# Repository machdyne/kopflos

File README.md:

# Kopflos Computer

Kopflos is a headless FPGA computer designed by Lone Dynamics Corporation.

This repo contains schematics, PCB layouts, pinouts, a 3D-printable case, example gateware and documentation.

Find more information on the [Kopflos product page](https://machdyne.com/product/kopflos-computer/).

## Programming Kopflos

Kopflos has a JTAG interface and ships with a [DFU bootloader](https://github.com/machdyne/tinydfu-bootloader) that allows the included flash [MMOD](https://machdyne.com/product/mmod) to be programmed over the USB-C port.

### DFU

The DFU bootloader is available for 5 seconds after power-on, issuing a DFU command during this period will stop the boot process until the DFU device is detached. If no command is received the boot process will continue and the user gateware will be loaded.

Install [dfu-util](http://dfu-util.sourceforge.net) (Debian/Ubuntu):

```
$ sudo apt install dfu-util
```

Update the user gateware on the flash MMOD:

```
$ sudo dfu-util -a 0 -D image.bit
```

Detach the DFU device and continue the boot process:

```
$ sudo dfu-util -a 0 -e
```

It is possible to update the bootloader itself using DFU but you shouldn't attempt this unless you have a JTAG programmer (or another method to program the MMOD) available, in case you need to restore the bootloader.

### JTAG

These examples assume you're using a "USB Blaster" JTAG cable, see the header pinout below. You will need to have [openFPGALoader](https://github.com/trabucayre/openFPGALoader) installed.

Program the configuration SRAM:

```
openFPGALoader -c usb-blaster image.bit
```

Program the flash MMOD:

```
openFPGALoader -f -c usb-blaster images/bootloader/tinydfu_kopflos.bit
```

## Blinky 

Building the blinky example requires [Yosys](https://github.com/YosysHQ/yosys), [nextpnr-ecp5](https://github.com/YosysHQ/nextpnr) and [Project Trellis](https://github.com/YosysHQ/prjtrellis).

Assuming they are installed, you can simply type `make` to build the gateware, which will be written to output/blinky.bin. You can then use [openFPGALoader](https://github.com/trabucayre/openFPGALoader) or dfu-util to write the gateware to the device.

## Linux

See the [Kakao Linux](https://github.com/machdyne/kakao) repo for detailed installation instructions.

## JTAG Header

The 3.3V JTAG header can be used to program the FPGA SRAM as well as the MMOD flash memory.

```
2 4 6
1 3 5
```

| Pin | Signal |
| --- | ------ |
| 1 | TCK |
| 2 | TDI |
| 3 | TDO |
| 4 | TMS |
| 5 | 3V3 (out) |
| 6 | GND |

## Board Revisions

| Revision | Notes |
| -------- | ----- |
| V0 | Initial version |

## License

The contents of this repo are released under the [Lone Dynamics Open License](LICENSE.md) with the following exceptions:

- The KiCad design files contain parts of the [kicad-pmod](https://github.com/mithro/kicad-pmod) library which is released under the [Apache License, Version 2.0](https://www.apache.org/licenses/LICENSE-2.0.html).

- The KiCad design files may contain symbols and footprints released under other licenses; please contact us if we've failed to give proper attribution.

Note: You can use these designs for commercial purposes but we ask that instead of producing exact clones, that you either replace our trademarks and logos with your own or add your own next to ours.

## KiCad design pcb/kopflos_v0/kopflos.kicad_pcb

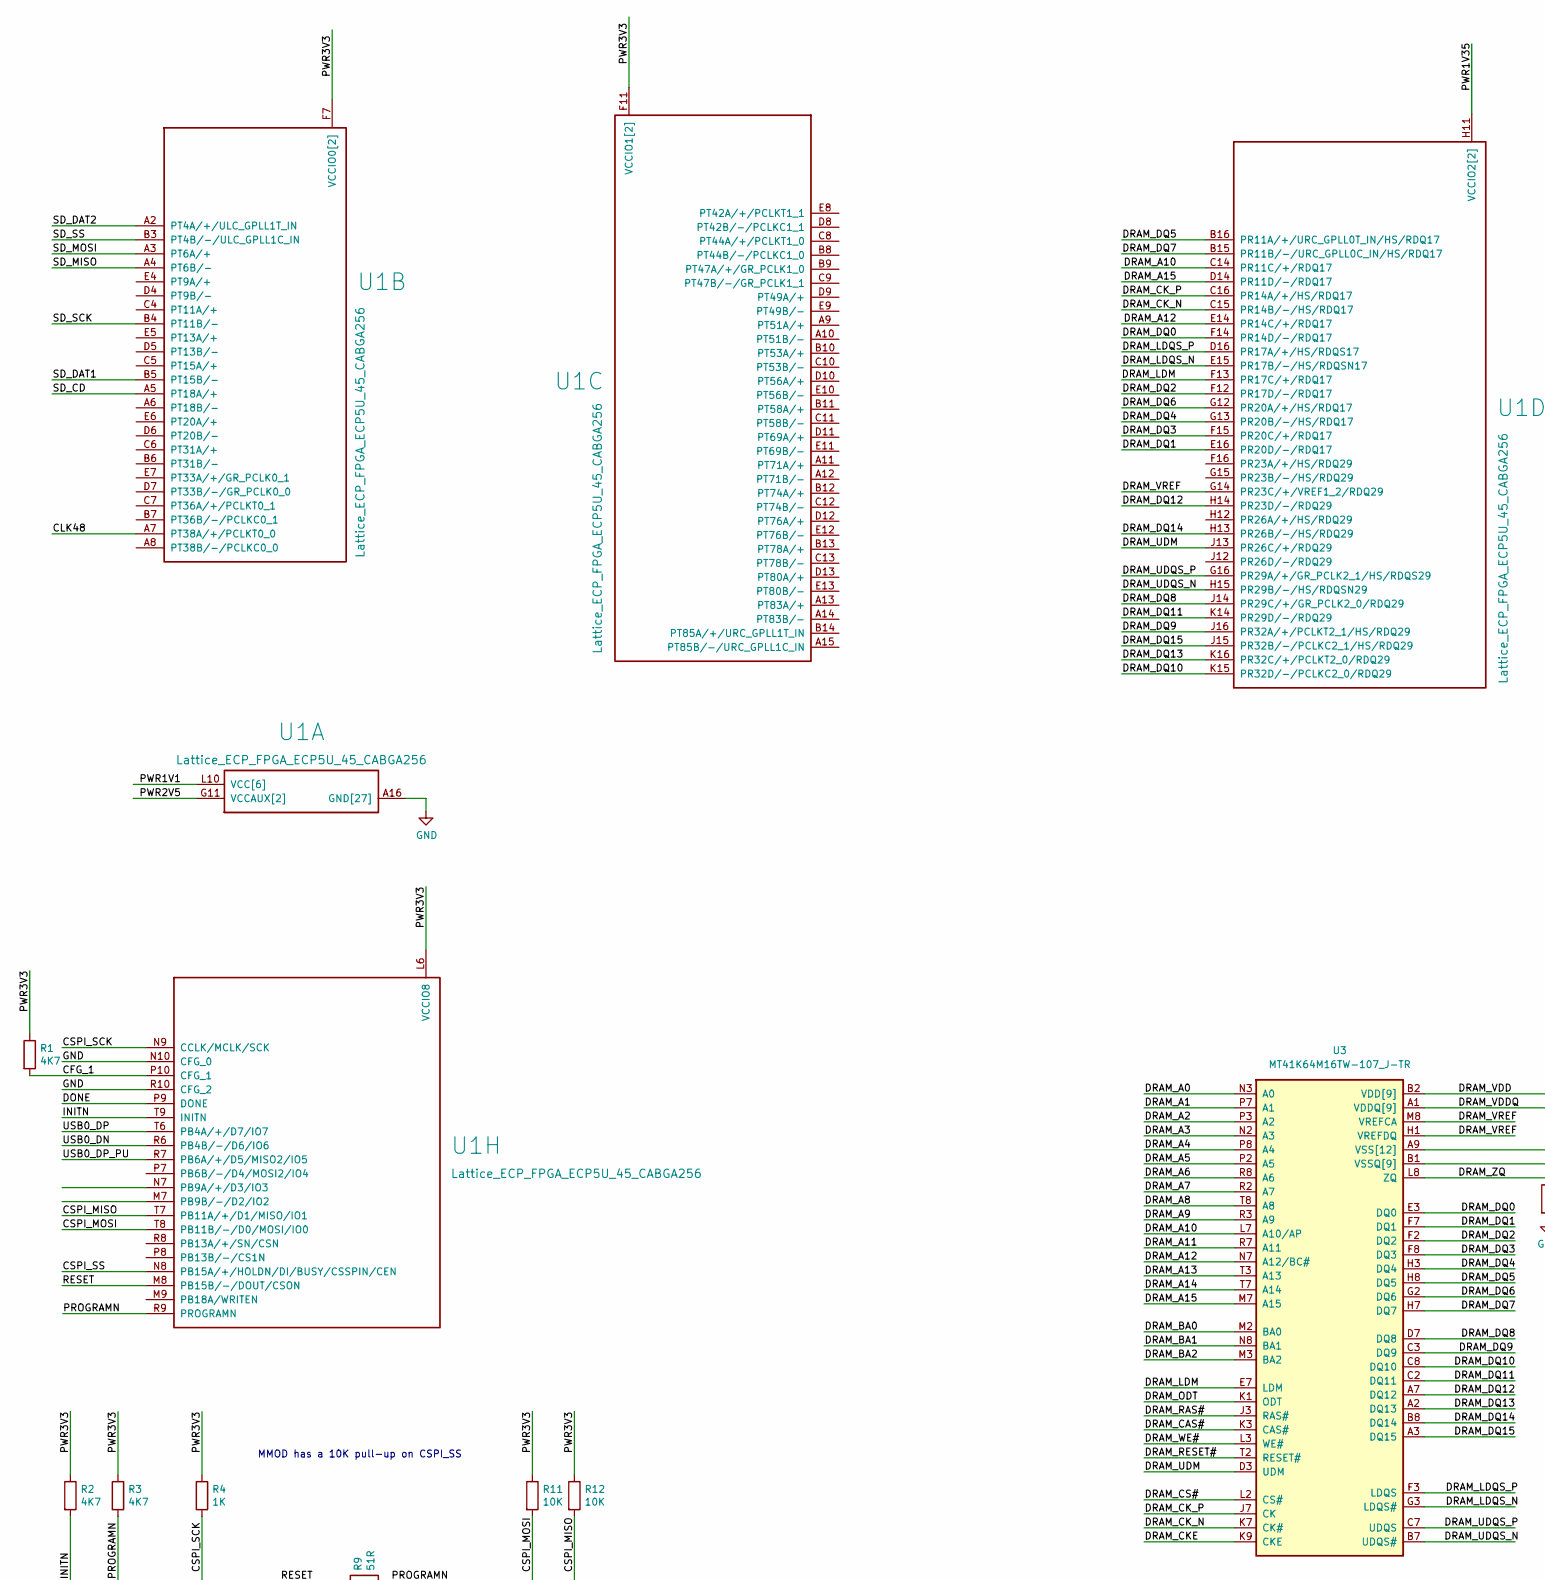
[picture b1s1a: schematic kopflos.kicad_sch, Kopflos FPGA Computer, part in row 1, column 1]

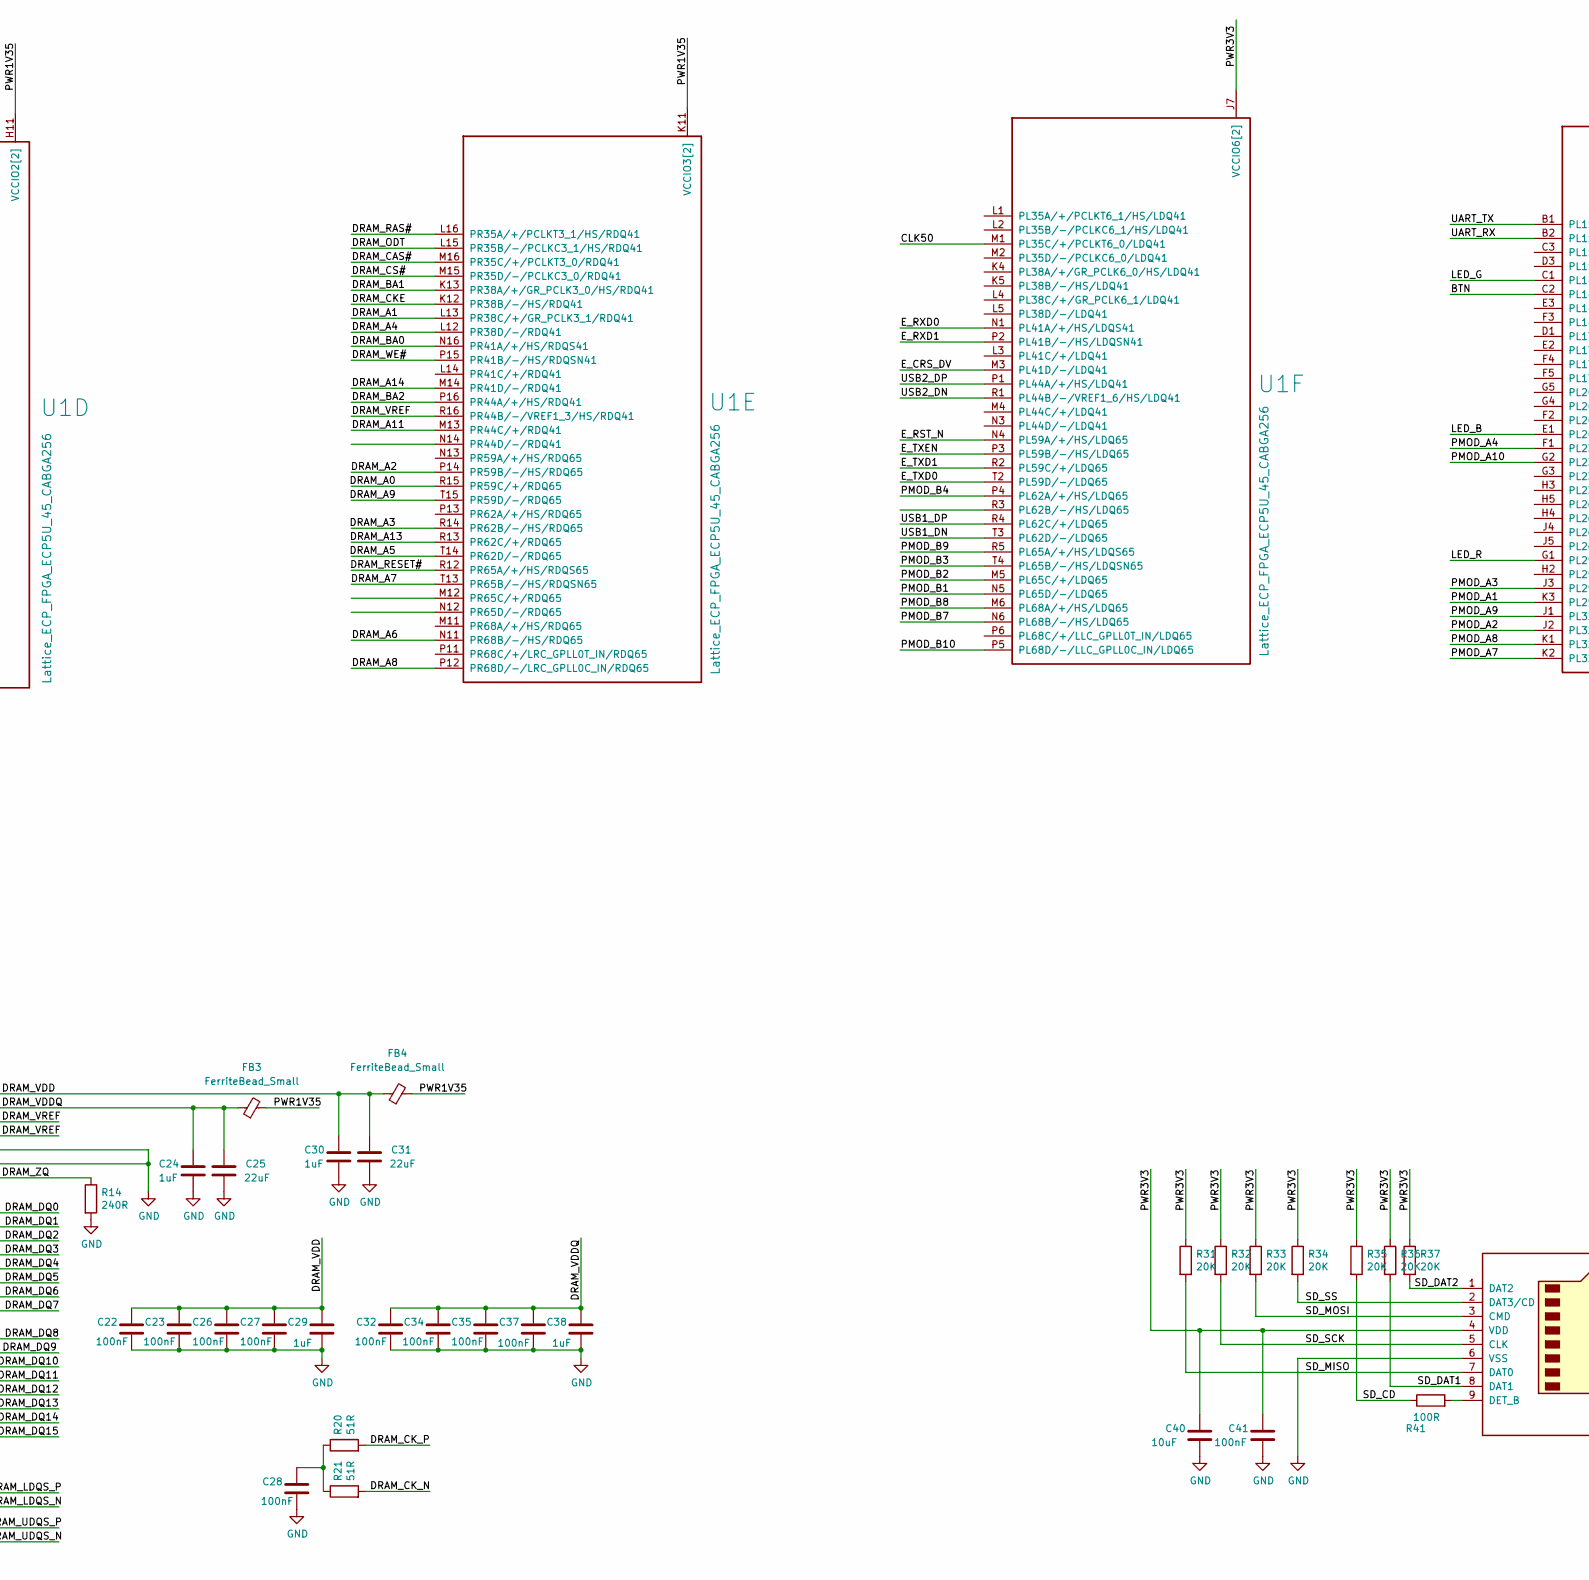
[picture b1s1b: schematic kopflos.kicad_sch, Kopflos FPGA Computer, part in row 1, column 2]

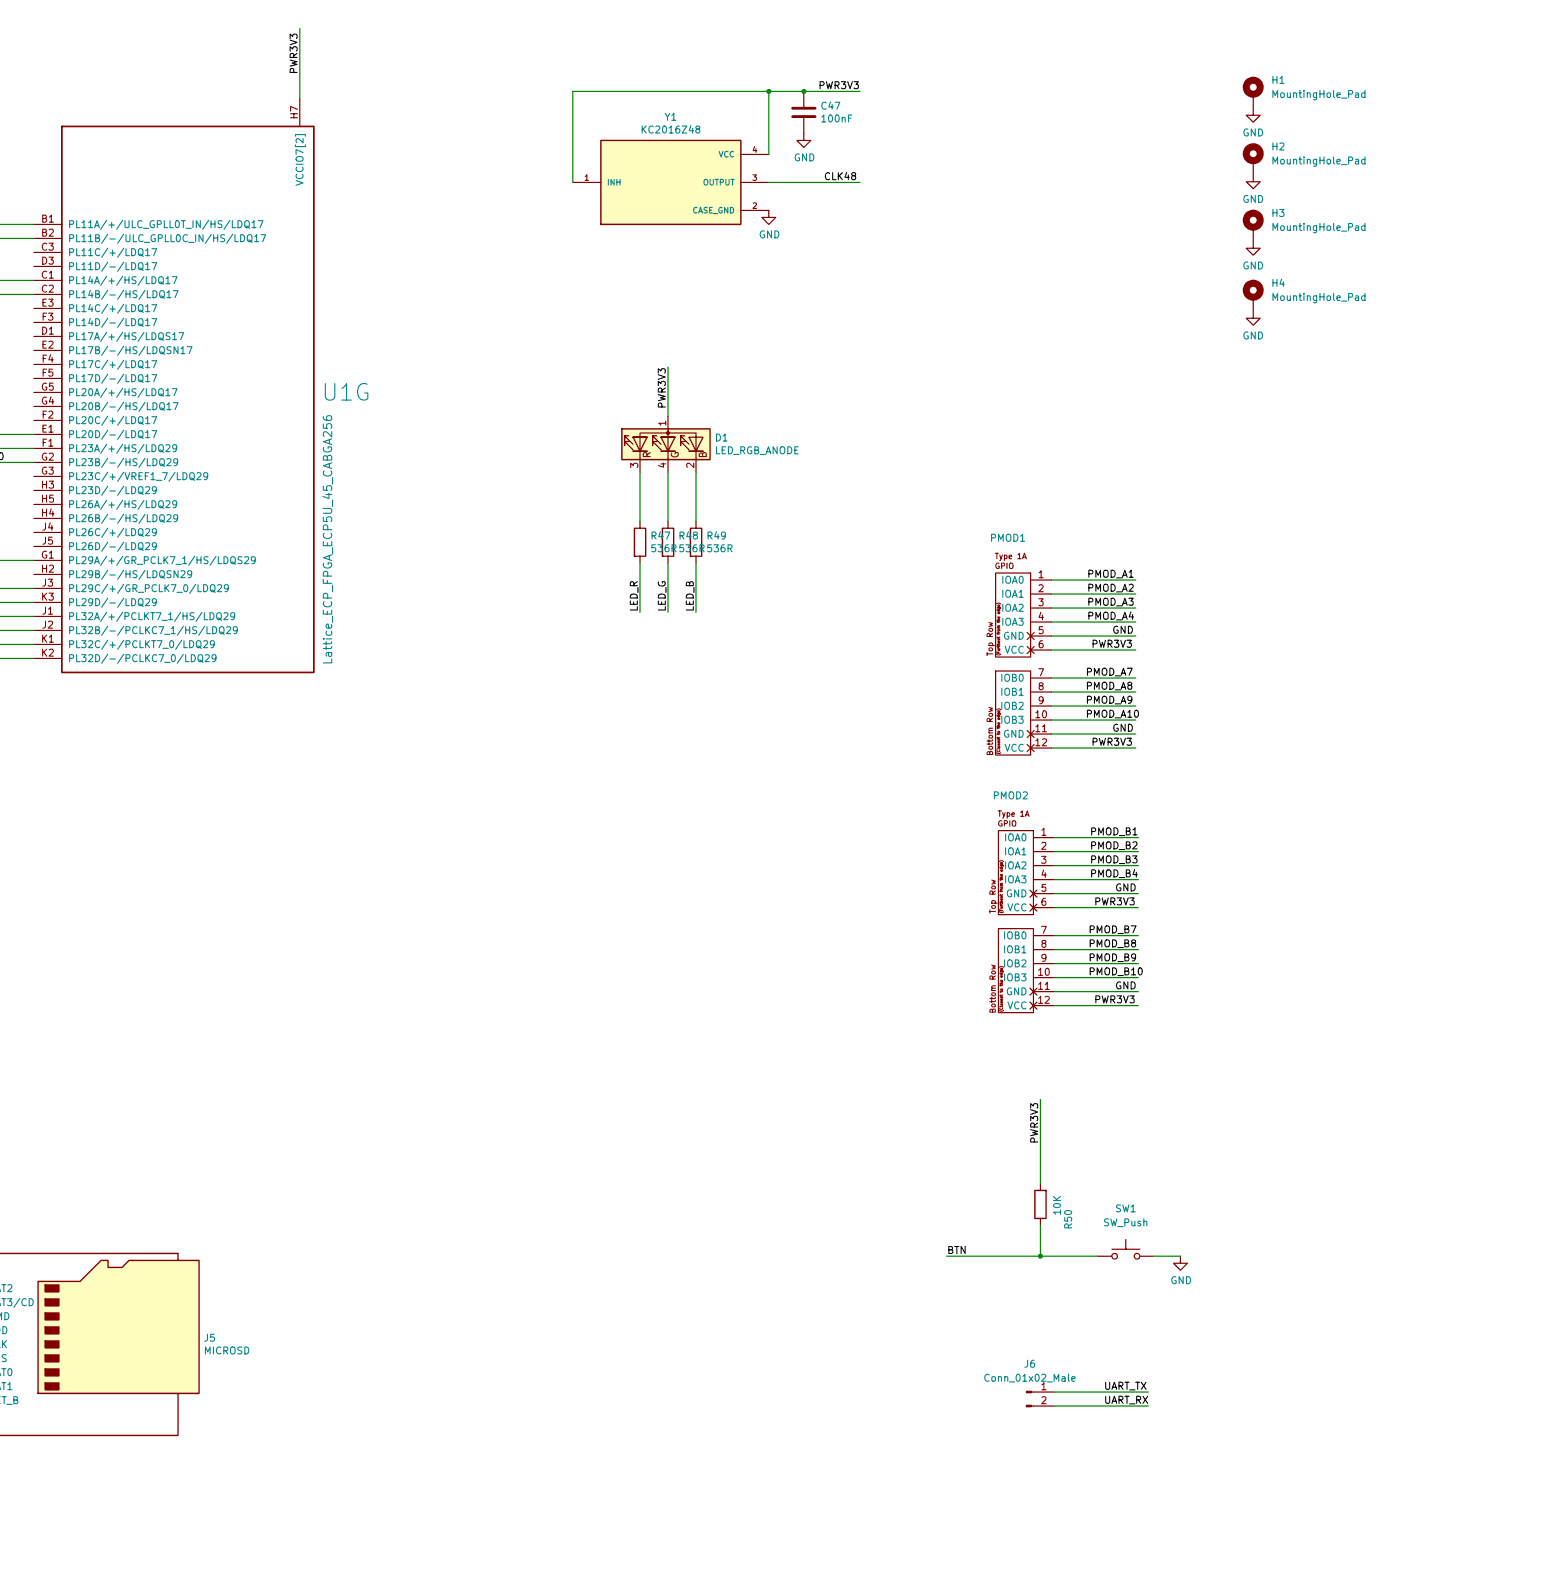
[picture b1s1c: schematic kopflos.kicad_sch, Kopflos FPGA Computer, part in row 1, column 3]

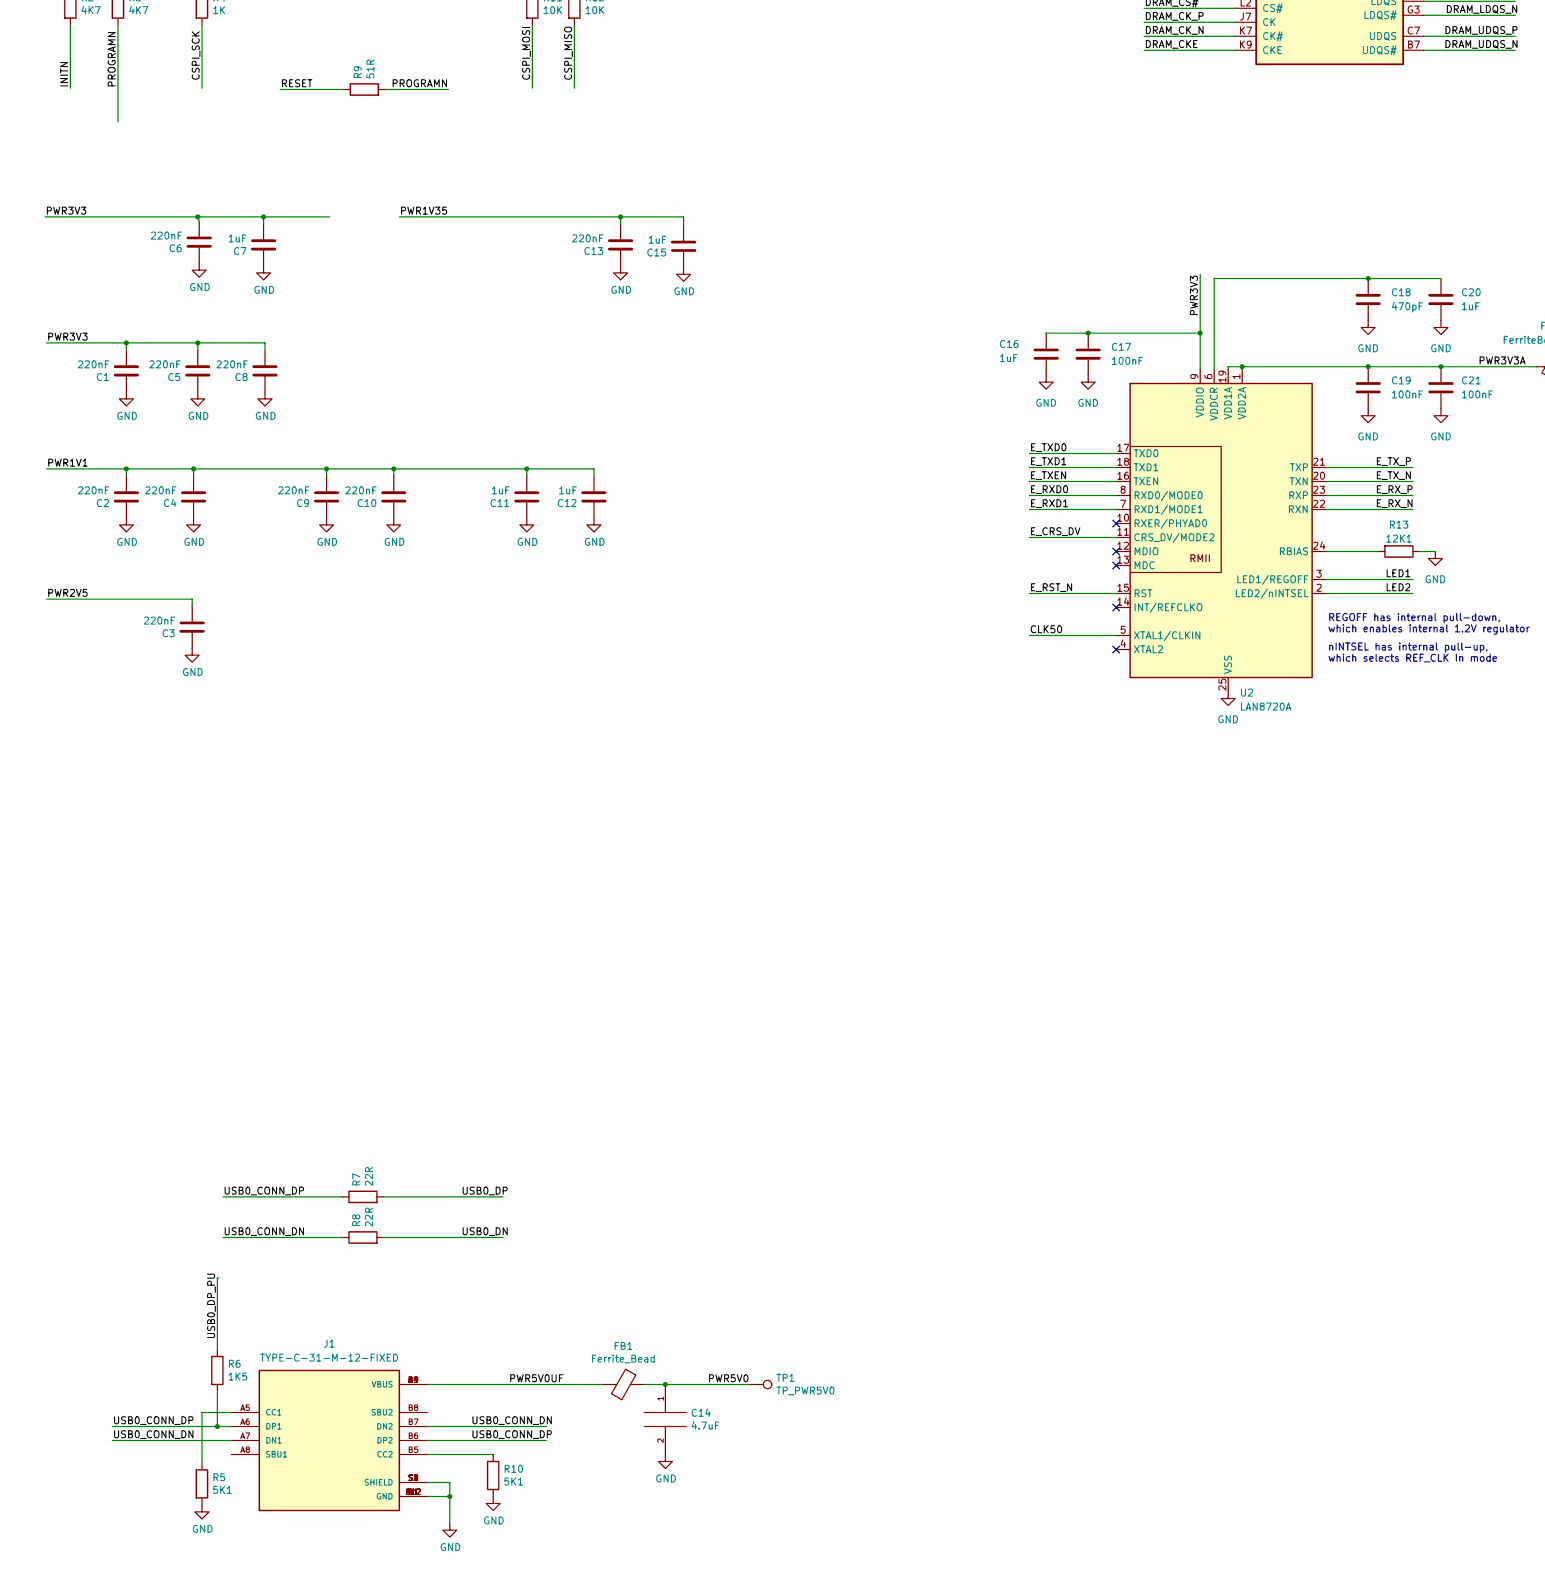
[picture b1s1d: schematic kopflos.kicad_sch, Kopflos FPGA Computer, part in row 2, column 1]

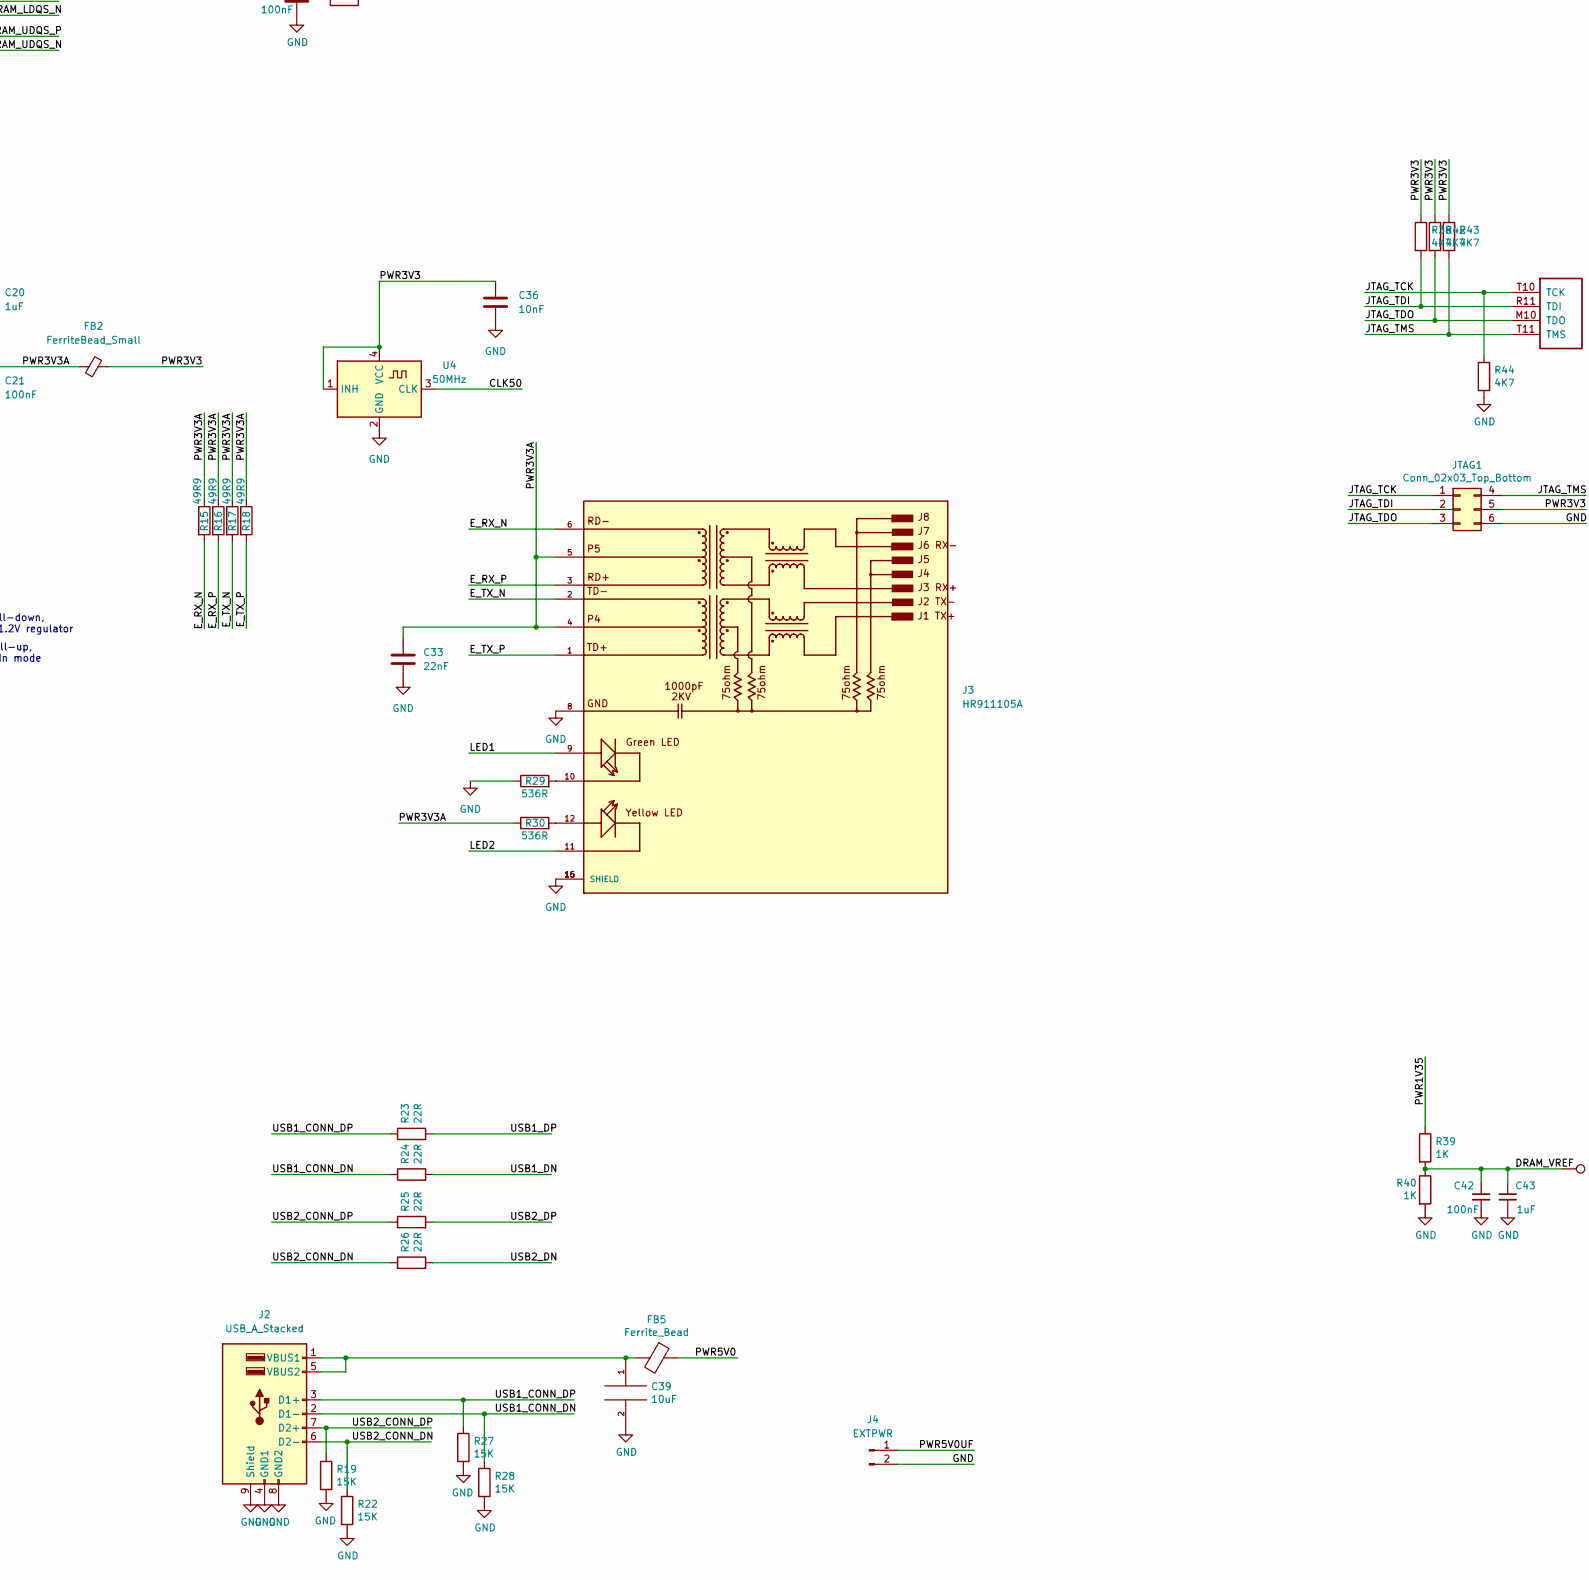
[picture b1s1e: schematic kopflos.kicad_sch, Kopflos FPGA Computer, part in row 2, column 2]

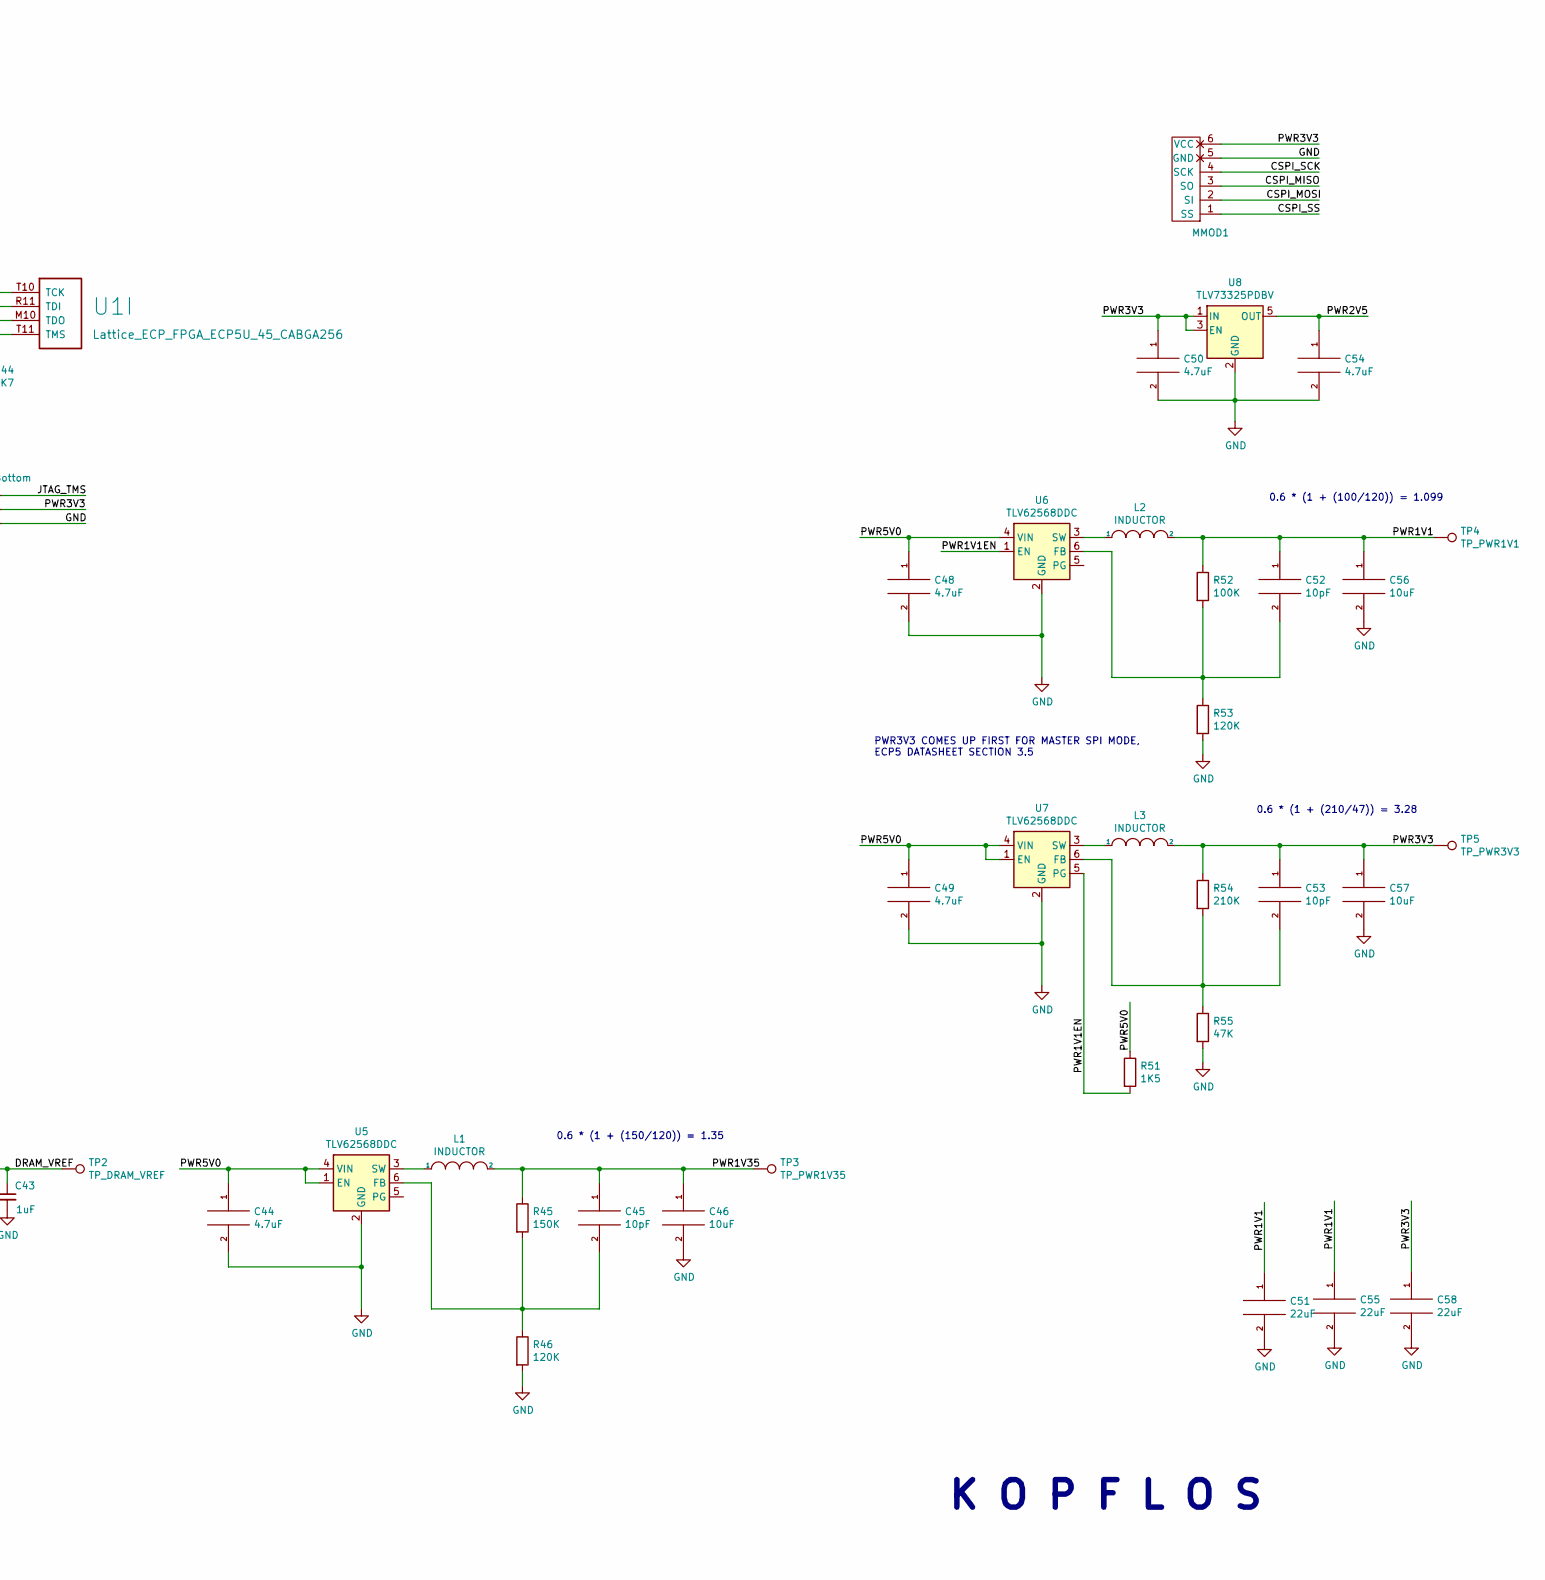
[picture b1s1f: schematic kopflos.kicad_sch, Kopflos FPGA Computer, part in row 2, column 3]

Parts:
C1, C2, C3, C4, C5, C6, C8, C9, C10, C13: 220nF; C_0603_1608Metric
C7, C11, C12, C15, C20, C43: 1uF; C_0603_1608Metric
C14, C44, C48, C49, C50, C54: 4.7uF; C_0603_1608Metric
C16, C24, C29, C30, C38: 1uF; C_0402_1005Metric
C17, C22, C23, C26, C27, C32, C34, C35, C37: 100nF; C_0402_1005Metric
C18: 470pF; C_0603_1608Metric
C19, C21, C42, C47: 100nF; C_0603_1608Metric
C25, C31: 22uF; R_0603_1608Metric
C28, C41: 100nF; R_0603_1608Metric
C33: 22nF; C_0603_1608Metric
C36: 10nF; C_0603_1608Metric
C39, C46, C56, C57: 10uF; C_0603_1608Metric
C40: 10uF; R_0603_1608Metric
C45, C52, C53: 10pF; C_0603_1608Metric
C51, C55, C58: 22uF; C_0603_1608Metric
D1: LED_RGB_ANODE; LED_RGB_0606_CHANZON
FB1, FB5: Ferrite_Bead; R_0603_1608Metric
FB2, FB3, FB4: FerriteBead_Small; R_0603_1608Metric
H1, H2, H3, H4: MountingHole_Pad; MountingHole_3.2mm_M3_Pad
J1: TYPE-C-31-M-12-FIXED; USB_C_Receptacle_HRO_TYPE-C-31-M-12-BIG-PADS; PARTREV A
J2: USB_A_Stacked; USB_A_Wuerth_61400826021_Horizontal_Stacked
J3: HR911105A; HANRUN_HR911105A; PARTREV A
J4: EXTPWR; PinHeader_1x02_P2.54mm_Vertical
J5: MICROSD; SDCARD
J6: Conn_01x02_Male; PinHeader_1x02_P2.54mm_Vertical
JTAG1: Conn_02x03_Top_Bottom; PinHeader_2x03_P2.54mm_Vertical
L1, L2, L3: INDUCTOR; L_0805_2012Metric
MMOD1: PMOD-Device-x1-Type-2-SPI; MMOD_Host_Socket
PMOD1, PMOD2: PMOD-Device-x2-Type-1A-GPIO; PMOD_2x06_HOST
R1, R2, R3, R38, R42, R43, R44: 4K7; R_0603_1608Metric
R4, R39, R40: 1K; R_0603_1608Metric
R5, R10: 5K1; R_0603_1608Metric
R6: 1K5; R_0402_1005Metric
R7, R8, R23, R24, R25, R26: 22R; R_0603_1608Metric
R9, R20, R21: 51R; R_0603_1608Metric
R11, R12, R50: 10K; R_0603_1608Metric
R13: 12K1; R_0603_1608Metric
R14: 240R; R_0603_1608Metric
R15, R16, R17, R18: 49R9; R_0603_1608Metric
R19, R22, R27, R28: 15K; R_0402_1005Metric
R29, R30, R47, R48, R49: 536R; R_0603_1608Metric
R31, R32, R33, R34, R35, R36, R37: 20K; R_0603_1608Metric
R41: 100R; R_0603_1608Metric
R45: 150K; R_0603_1608Metric
R46, R53: 120K; R_0603_1608Metric
R51: 1K5; R_0603_1608Metric
R52: 100K; R_0603_1608Metric
R54: 210K; R_0603_1608Metric
R55: 47K; R_0603_1608Metric
SW1: SW_Push; Button_2P_3x4mm
TP1: TP_PWR5V0; TestPoint_THTPad_D1.0mm_Drill0.5mm
TP2: TP_DRAM_VREF; TestPoint_THTPad_D1.0mm_Drill0.5mm
TP3: TP_PWR1V35; TestPoint_THTPad_D1.0mm_Drill0.5mm
TP4: TP_PWR1V1; TestPoint_THTPad_D1.0mm_Drill0.5mm
TP5: TP_PWR3V3; TestPoint_THTPad_D1.0mm_Drill0.5mm
U1: Lattice_ECP_FPGA_ECP5U_45_CABGA256; BGA-256_14.0x14.0mm_Layout16x16_P0.8mm_Ball0.45mm_Pad0.32mm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
U2: LAN8720A; QFN-24-1EP_4x4mm_P0.5mm_EP2.6x2.6mm
U3: MT41K64M16TW-107_J-TR; BGA-96_9.0x13.0mm_Layout2x3x16_P0.8mm
U4: 50MHz; Oscillator_SMD_Kyocera_KC2520Z-4Pin_2.5x2.0mm
U5, U6, U7: TLV62568DDC; SOT-23-6
U8: TLV73325PDBV; SOT-23-5
Y1: KC2016Z48; OSC_KC2016Z13.5600C1KX00; PARTREV November 2020

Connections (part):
/BTN: R50.1, SW1.1, U1.C2 (PL14B/-/HS/LDQ17)
/CFG_1: R1.2, U1.P10 (CFG_1)
/CLK48: U1.A7 (PT38A/+/PCLKT0_0), Y1.3 (OUTPUT)
/CLK50: U1.M1 (PL35C/+/PCLKT6_0/LDQ41), U2.5 (XTAL1/CLKIN), U4.3 (CLK)
/CSPI_MISO: MMOD1.3 (SO), R12.2, U1.T7 (PB11A/+/D1/MISO/IO1)
/CSPI_MOSI: MMOD1.2 (SI), R11.2, U1.T8 (PB11B/-/D0/MOSI/IO0)
/CSPI_SCK: MMOD1.4 (SCK), R4.2, U1.N9 (CCLK/MCLK/SCK)
/CSPI_SS: MMOD1.1 (SS), U1.N8 (PB15A/+/HOLDN/DI/BUSY/CSSPIN/CEN)
/DONE: U1.P9 (DONE)
/DRAM_A0: U1.R15 (PR59C/+/RDQ65), U3.N3 (A0)
/DRAM_A1: U1.L13 (PR38C/+/GR_PCLK3_1/RDQ41), U3.P7 (A1)
/DRAM_A2: U1.P14 (PR59B/-/HS/RDQ65), U3.P3 (A2)
/DRAM_A3: U1.R14 (PR62B/-/HS/RDQ65), U3.N2 (A3)
/DRAM_A4: U1.L12 (PR38D/-/RDQ41), U3.P8 (A4)
/DRAM_A5: U1.T14 (PR62D/-/RDQ65), U3.P2 (A5)
/DRAM_A6: U1.N11 (PR68B/-/HS/RDQ65), U3.R8 (A6)
/DRAM_A7: U1.T13 (PR65B/-/HS/RDQSN65), U3.R2 (A7)
/DRAM_A8: U1.P12 (PR68D/-/LRC_GPLL0C_IN/RDQ65), U3.T8 (A8)
/DRAM_A9: U1.T15 (PR59D/-/RDQ65), U3.R3 (A9)
/DRAM_A10: U1.C14 (PR11C/+/RDQ17), U3.L7 (A10/AP)
/DRAM_A11: U1.M13 (PR44C/+/RDQ41), U3.R7 (A11)
/DRAM_A12: U1.E14 (PR14C/+/RDQ17), U3.N7 (A12/BC#)
/DRAM_A13: U1.R13 (PR62C/+/RDQ65), U3.T3 (A13)
/DRAM_A14: U1.M14 (PR41D/-/RDQ41), U3.T7 (A14)
/DRAM_A15: U1.D14 (PR11D/-/RDQ17), U3.M7 (A15)
/DRAM_BA0: U1.N16 (PR41A/+/HS/RDQS41), U3.M2 (BA0)
/DRAM_BA1: U1.K13 (PR38A/+/GR_PCLK3_0/HS/RDQ41), U3.N8 (BA1)
/DRAM_BA2: U1.P16 (PR44A/+/HS/RDQ41), U3.M3 (BA2)
/DRAM_CAS#: U1.M16 (PR35C/+/PCLKT3_0/RDQ41), U3.K3 (CAS#)
/DRAM_CKE: U1.K12 (PR38B/-/HS/RDQ41), U3.K9 (CKE)
/DRAM_CK_N: R21.2, U1.C15 (PR14B/-/HS/RDQ17), U3.K7 (CK#)
/DRAM_CK_P: R20.2, U1.C16 (PR14A/+/HS/RDQ17), U3.J7 (CK)
/DRAM_CS#: U1.M15 (PR35D/-/PCLKC3_0/RDQ41), U3.L2 (CS#)
/DRAM_DQ0: U1.F14 (PR14D/-/RDQ17), U3.E3 (DQ0)
/DRAM_DQ1: U1.E16 (PR20D/-/RDQ17), U3.F7 (DQ1)
/DRAM_DQ2: U1.F12 (PR17D/-/RDQ17), U3.F2 (DQ2)
/DRAM_DQ3: U1.F15 (PR20C/+/RDQ17), U3.F8 (DQ3)
/DRAM_DQ4: U1.G13 (PR20B/-/HS/RDQ17), U3.H3 (DQ4)
/DRAM_DQ5: U1.B16 (PR11A/+/URC_GPLL0T_IN/HS/RDQ17), U3.H8 (DQ5)
/DRAM_DQ6: U1.G12 (PR20A/+/HS/RDQ17), U3.G2 (DQ6)
/DRAM_DQ7: U1.B15 (PR11B/-/URC_GPLL0C_IN/HS/RDQ17), U3.H7 (DQ7)
/DRAM_DQ8: U1.J14 (PR29C/+/GR_PCLK2_0/RDQ29), U3.D7 (DQ8)
/DRAM_DQ9: U1.J16 (PR32A/+/PCLKT2_1/HS/RDQ29), U3.C3 (DQ9)
/DRAM_DQ10: U1.K15 (PR32D/-/PCLKC2_0/RDQ29), U3.C8 (DQ10)
/DRAM_DQ11: U1.K14 (PR29D/-/RDQ29), U3.C2 (DQ11)
/DRAM_DQ12: U1.H14 (PR23D/-/RDQ29), U3.A7 (DQ12)
/DRAM_DQ13: U1.K16 (PR32C/+/PCLKT2_0/RDQ29), U3.A2 (DQ13)
/DRAM_DQ14: U1.H13 (PR26B/-/HS/RDQ29), U3.B8 (DQ14)
/DRAM_DQ15: U1.J15 (PR32B/-/PCLKC2_1/HS/RDQ29), U3.A3 (DQ15)
/DRAM_LDM: U1.F13 (PR17C/+/RDQ17), U3.E7 (LDM)
/DRAM_LDQS_N: U1.E15 (PR17B/-/HS/RDQSN17), U3.G3 (LDQS#)
/DRAM_LDQS_P: U1.D16 (PR17A/+/HS/RDQS17), U3.F3 (LDQS)
/DRAM_ODT: U1.L15 (PR35B/-/PCLKC3_1/HS/RDQ41), U3.K1 (ODT)
/DRAM_RAS#: U1.L16 (PR35A/+/PCLKT3_1/HS/RDQ41), U3.J3 (RAS#)
/DRAM_RESET#: U1.R12 (PR65A/+/HS/RDQS65), U3.T2 (RESET#)
/DRAM_UDM: U1.J13 (PR26C/+/RDQ29), U3.D3 (UDM)
/DRAM_UDQS_N: U1.H15 (PR29B/-/HS/RDQSN29), U3.B7 (UDQS#)
/DRAM_UDQS_P: U1.G16 (PR29A/+/GR_PCLK2_1/HS/RDQS29), U3.C7 (UDQS)
/DRAM_VDD: C22.1, C23.1, C26.1, C27.1, C29.1, C30.1, C31.1, FB4.1, U3.B2 (VDD[9]), U3.D9 (VDD), U3.G7 (VDD), U3.K2 (VDD), U3.K8 (VDD), U3.N1 (VDD), U3.N9 (VDD), U3.R1 (VDD), U3.R9 (VDD)
/DRAM_VDDQ: C24.1, C25.1, C32.1, C34.1, C35.1, C37.1, C38.1, FB3.1, U3.A1 (VDDQ[9]), U3.A8 (VDDQ), U3.C1 (VDDQ), U3.C9 (VDDQ), U3.D2 (VDDQ), U3.E9 (VDDQ), U3.F1 (VDDQ), U3.H2 (VDDQ), U3.H9 (VDDQ)
/DRAM_VREF: C42.1, C43.1, R39.2, R40.1, TP2.1, U1.G14 (PR23C/+/VREF1_2/RDQ29), U1.R16 (PR44B/-/VREF1_3/HS/RDQ41), U3.H1 (VREFDQ), U3.M8 (VREFCA)
/DRAM_WE#: U1.P15 (PR41B/-/HS/RDQSN41), U3.L3 (WE#)
/DRAM_ZQ: R14.1, U3.L8 (ZQ)
/E_CRS_DV: U1.M3 (PL41D/-/LDQ41), U2.11 (CRS_DV/MODE2)
/E_RST_N: U1.N4 (PL59A/+/HS/LDQ65), U2.15 (RST)
/E_RXD0: U1.N1 (PL41A/+/HS/LDQS41), U2.8 (RXD0/MODE0)
/E_RXD1: U1.P2 (PL41B/-/HS/LDQSN41), U2.7 (RXD1/MODE1)
/E_RX_N: J3.6, R15.2, U2.22 (RXN)
/E_RX_P: J3.3, R16.2, U2.23 (RXP)
/E_TXD0: U1.T2 (PL59D/-/LDQ65), U2.17 (TXD0)
/E_TXD1: U1.R2 (PL59C/+/LDQ65), U2.18 (TXD1)
/E_TXEN: U1.P3 (PL59B/-/HS/LDQ65), U2.16 (TXEN)
/E_TX_N: J3.2, R17.2, U2.20 (TXN)
/E_TX_P: J3.1, R18.2, U2.21 (TXP)
/INITN: R2.2, U1.T9 (INITN)
/JTAG_TCK: JTAG1.1, R44.1, U1.T10 (TCK)
/JTAG_TDI: JTAG1.2, R38.2, U1.R11 (TDI)
/JTAG_TDO: JTAG1.3, R42.2, U1.M10 (TDO)
/JTAG_TMS: JTAG1.4, R43.2, U1.T11 (TMS)
/LED1: J3.9, U2.3 (LED1/REGOFF)
/LED2: J3.11, U2.2 (LED2/nINTSEL)
/LED_B: R49.2, U1.E1 (PL20D/-/LDQ17)
/LED_G: R48.2, U1.C1 (PL14A/+/HS/LDQ17)
/LED_R: R47.2, U1.G1 (PL29A/+/GR_PCLK7_1/HS/LDQS29)
/PMOD_A1: PMOD1.1 (IOA0), U1.K3 (PL29D/-/LDQ29)
/PMOD_A2: PMOD1.2 (IOA1), U1.J2 (PL32B/-/PCLKC7_1/HS/LDQ29)
/PMOD_A3: PMOD1.3 (IOA2), U1.J3 (PL29C/+/GR_PCLK7_0/LDQ29)
/PMOD_A4: PMOD1.4 (IOA3), U1.F1 (PL23A/+/HS/LDQ29)
/PMOD_A7: PMOD1.7 (IOB0), U1.K2 (PL32D/-/PCLKC7_0/LDQ29)
/PMOD_A8: PMOD1.8 (IOB1), U1.K1 (PL32C/+/PCLKT7_0/LDQ29)
/PMOD_A9: PMOD1.9 (IOB2), U1.J1 (PL32A/+/PCLKT7_1/HS/LDQ29)
/PMOD_A10: PMOD1.10 (IOB3), U1.G2 (PL23B/-/HS/LDQ29)
/PMOD_B1: PMOD2.1 (IOA0), U1.N5 (PL65D/-/LDQ65)
/PMOD_B2: PMOD2.2 (IOA1), U1.M5 (PL65C/+/LDQ65)
/PMOD_B3: PMOD2.3 (IOA2), U1.T4 (PL65B/-/HS/LDQSN65)
/PMOD_B4: PMOD2.4 (IOA3), U1.P4 (PL62A/+/HS/LDQ65)
/PMOD_B7: PMOD2.7 (IOB0), U1.N6 (PL68B/-/HS/LDQ65)
/PMOD_B8: PMOD2.8 (IOB1), U1.M6 (PL68A/+/HS/LDQ65)
/PMOD_B9: PMOD2.9 (IOB2), U1.R5 (PL65A/+/HS/LDQS65)
/PMOD_B10: PMOD2.10 (IOB3), U1.P5 (PL68D/-/LLC_GPLL0C_IN/LDQ65)
/PROGRAMN: R3.2, R9.2, U1.R9 (PROGRAMN)
/PWR1V1: C2.2, C4.2, C9.2, C10.2, C11.2, C12.2, C51.1, C52.1, C55.1, C56.1, L2.2, R52.1, TP4.1, U1.G6 (VCC[6]), U1.G7 (VCC[6]), U1.G9 (VCC[6]), U1.L8 (VCC[6]), U1.L9 (VCC[6]), U1.L10 (VCC[6])
/PWR1V1EN: R51.2, U6.1 (EN), U7.5 (PG)
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
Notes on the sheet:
K O P F L O S
nINTSEL has internal pull-up, which selects REF_CLK In mode
PWR3V3 COMES UP FIRST FOR MASTER SPI MODE, ECP5 DATASHEET SECTION 3.5
0.6 * (1 + (210/47)) = 3.28
REGOFF has internal pull-down, which enables internal 1.2V regulator
MMOD has a 10K pull-up on CSPI_SS
0.6 * (1 + (100/120)) = 1.099
0.6 * (1 + (150/120)) = 1.35

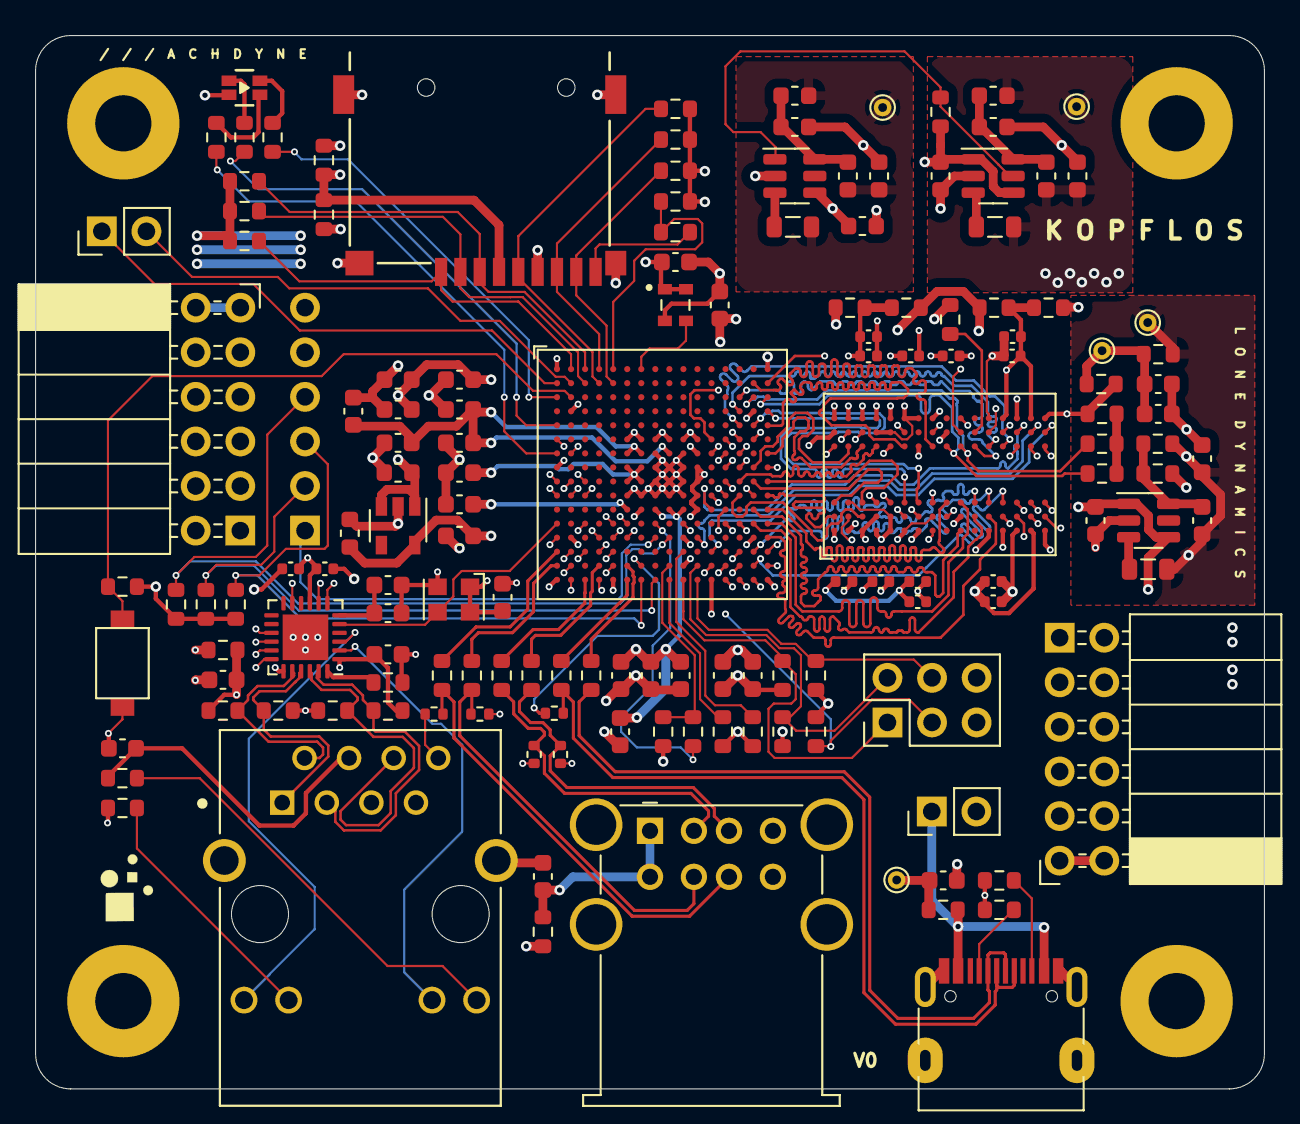
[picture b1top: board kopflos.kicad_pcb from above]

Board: 6 copper layers, 70.0 x 60.0 mm, 151 parts (1 on the bottom side), 150 nets.

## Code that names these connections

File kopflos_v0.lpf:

BLOCK RESETPATHS;
BLOCK ASYNCPATHS;

# CLOCK
LOCATE COMP "CLK_48" SITE "A7";
IOBUF  PORT "CLK_48" PULLMODE=NONE IO_TYPE=LVCMOS33;
FREQUENCY PORT "CLK_48" 48 MHZ;

SYSCONFIG CONFIG_IOVOLTAGE=3.3 COMPRESS_CONFIG=ON MCCLK_FREQ=2.4 MASTER_SPI_PORT=ENABLE SLAVE_SPI_PORT=DISABLE SLAVE_PARALLEL_PORT=DISABLE CONFIG_MODE=SPI_SERIAL;

LOCATE COMP "LED_R" SITE "G1";
IOBUF  PORT "LED_R" PULLMODE=NONE IO_TYPE=LVCMOS33 DRIVE=4;

LOCATE COMP "LED_G" SITE "C1";
IOBUF  PORT "LED_G" PULLMODE=NONE IO_TYPE=LVCMOS33 DRIVE=4;

LOCATE COMP "LED_B" SITE "E1";
IOBUF  PORT "LED_B" PULLMODE=NONE IO_TYPE=LVCMOS33 DRIVE=4;

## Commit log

2023-02-21 add image
2023-03-02 update images
2023-05-08 add pcb
2025-03-22 fix usb host clock

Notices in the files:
pcb/kopflos_v0/kopflos.kicad_sch:
Copyright © 2023 Lone Dynamics Corporation
